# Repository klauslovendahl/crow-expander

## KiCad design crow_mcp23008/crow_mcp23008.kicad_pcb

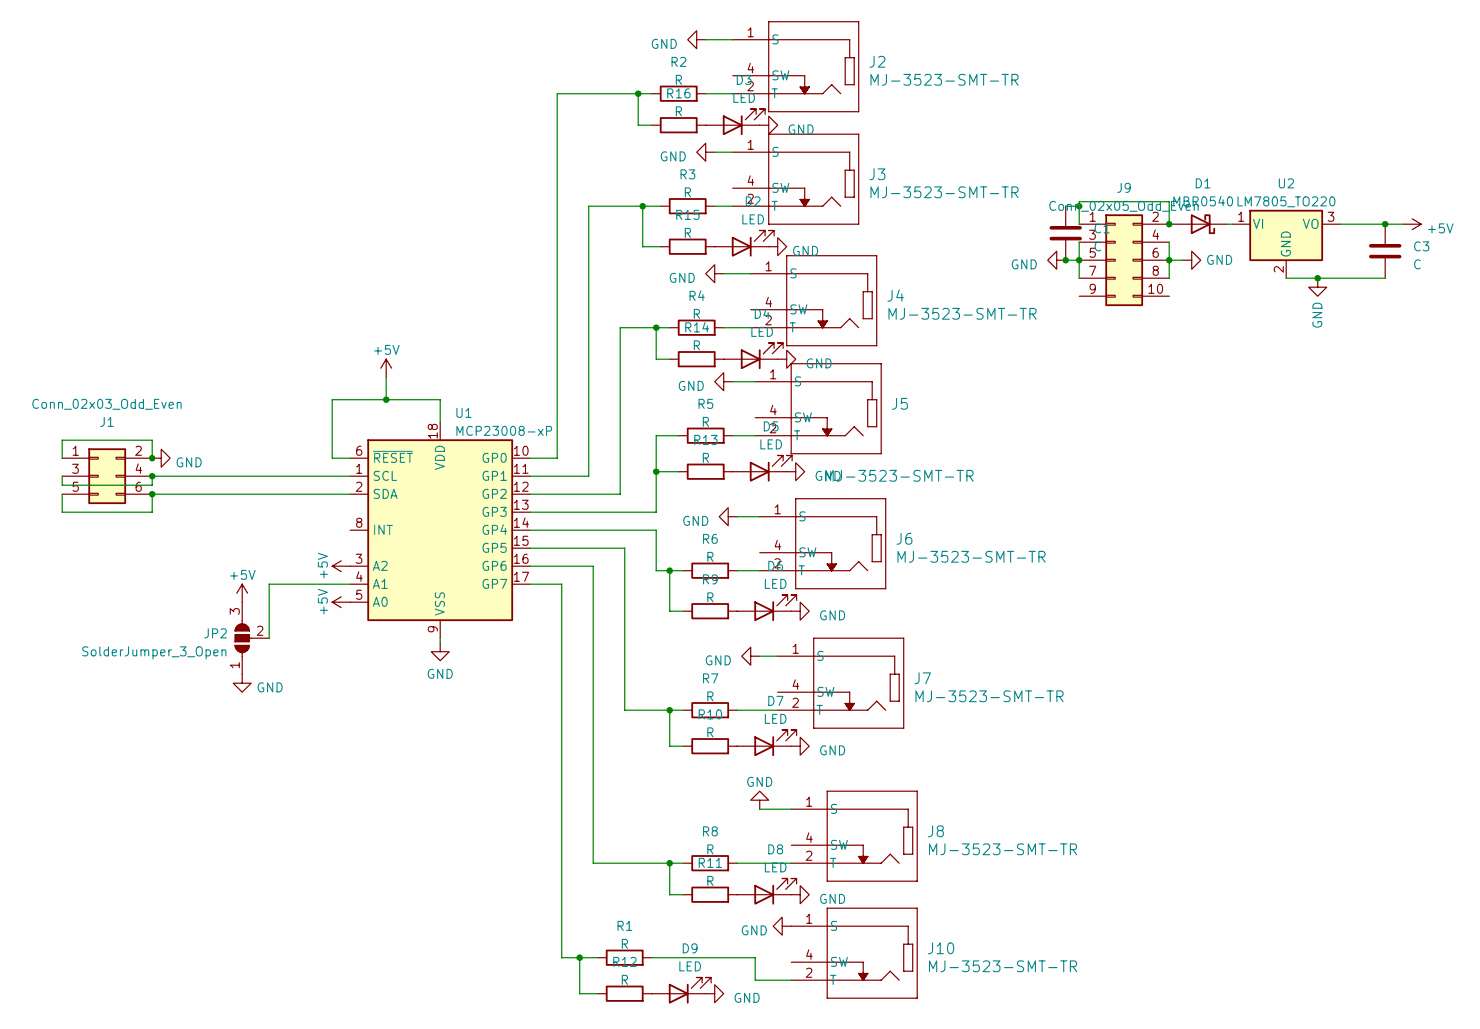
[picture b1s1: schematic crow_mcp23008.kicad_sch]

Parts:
C1, C3: C; C_1206_3216Metric_Pad1.33x1.80mm_HandSolder
D1: MBR0540; D_SOD-123
D2, D3, D4, D5, D6, D7, D8, D9: LED; LED_1206_3216Metric_Pad1.42x1.75mm_HandSolder
J1: Conn_02x03_Odd_Even; PinHeader_2x03_P2.54mm_Horizontal
J2, J3, J4, J5, J6, J7, J8, J10: MJ-3523-SMT-TR; CONN_MJ-3523_CUD
J9: Conn_02x05_Odd_Even; PinHeader_2x05_P2.54mm_Horizontal
JP2: SolderJumper_3_Open; SolderJumper-3_P2.0mm_Open_TrianglePad1.0x1.5mm_NumberLabels
R1, R2, R3, R4, R5, R6, R7, R8, R9, R10, R11, R12, R13, R14, R15, R16: R; R_1206_3216Metric_Pad1.30x1.75mm_HandSolder
U1: MCP23008-xP; SOIC-18W_7.5x11.6mm_P1.27mm
U2: LM7805_TO220; SOT-223-3_TabPin2

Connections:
+5V: C3.1, JP2.3 (B), U1.3 (A2), U1.5 (A0), U1.6 (~RESET), U1.18 (VDD), U2.3 (VO)
GND: C1.2, C3.2, D2.1 (K), D3.1 (K), D4.1 (K), D5.1 (K), D6.1 (K), D7.1 (K), D8.1 (K), D9.1 (K), J1.1, J1.2, J2.1 (S), J3.1 (S), J4.1 (S), J5.1 (S), J6.1 (S), J7.1 (S), J8.1 (S), J9.3, J9.4, J9.5, J9.6, J9.7, J9.8, J10.1 (S), JP2.1 (A), U1.9 (VSS), U2.2 (GND)
unnamed: C1.1, D1.2 (A), J9.1, J9.2
unnamed: D1.1 (K), U2.1 (VI)
unnamed: D2.2 (A), R15.2
unnamed: D3.2 (A), R16.2
unnamed: D4.2 (A), R14.2
unnamed: D5.2 (A), R13.2
unnamed: D6.2 (A), R9.2
unnamed: D7.2 (A), R10.2
unnamed: D8.2 (A), R11.2
unnamed: D9.2 (A), R12.2
unnamed: J1.3, J1.4, U1.1 (SCL)
unnamed: J1.5, J1.6, U1.2 (SDA)
unnamed: J2.2 (T), R2.2
unnamed: J3.2 (T), R3.2
unnamed: J4.2 (T), R4.2
unnamed: J5.2 (T), R5.2
unnamed: J6.2 (T), R6.2
unnamed: J7.2 (T), R7.2
unnamed: J8.2 (T), R8.2
unnamed: J10.2 (T), R1.2
unnamed: JP2.2 (C), U1.4 (A1)
unnamed: R2.1, R16.1, U1.10 (GP0)
unnamed: R3.1, R15.1, U1.11 (GP1)
unnamed: R4.1, R14.1, U1.12 (GP2)
unnamed: R5.1, R13.1, U1.13 (GP3)
unnamed: R6.1, R9.1, U1.14 (GP4)
unnamed: R7.1, R10.1, U1.15 (GP5)
unnamed: R8.1, R11.1, U1.16 (GP6)
unnamed: R1.1, R12.1, U1.17 (GP7)

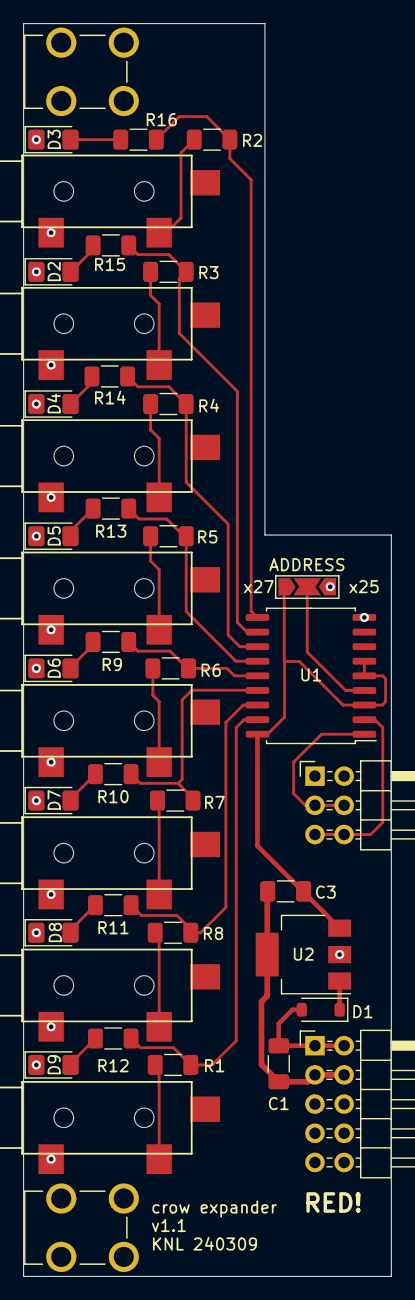
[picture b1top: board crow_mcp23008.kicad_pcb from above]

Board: 2 copper layers, 32.0 x 109.0 mm, 41 parts (0 on the bottom side), 31 nets.

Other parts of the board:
KEYSTONE7773: KEYSTONE_7773

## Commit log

2024-01-28 initial board
    v1 design ordered 240127
2024-03-10 v1.1
    all SMT w/ LED's
2024-03-10 added front panel
    front panel v1, ordered in 5052 aluminum
2024-03-10 added plastic panel
    panel for cutting from acrylic - no holes for LEDs
